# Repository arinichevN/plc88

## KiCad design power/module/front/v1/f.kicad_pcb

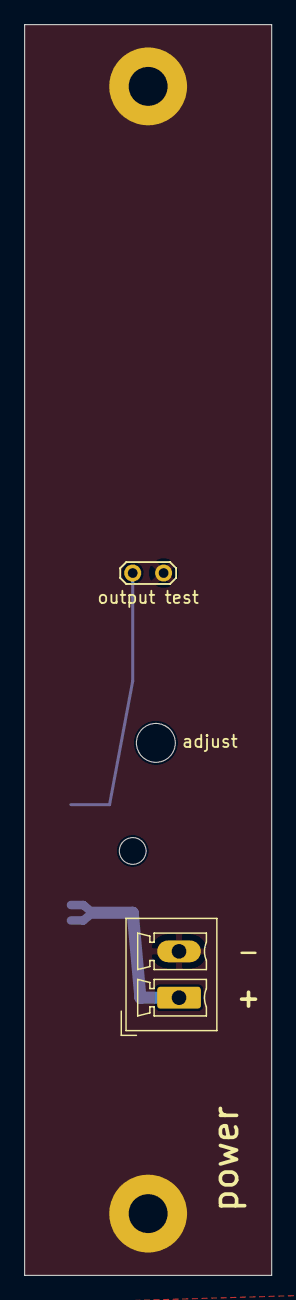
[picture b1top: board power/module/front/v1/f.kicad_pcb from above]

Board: 2 copper layers, 20.3 x 102.9 mm, 7 parts (0 on the bottom side), 3 nets.

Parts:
H1, H2: MountingHole_Pad; MountingHole_3.2mm_M3_Pad
H3: adjust; MountingHole_3.2mm_M3_DIN965
H4: power led; MountingHole_2.2mm_M2_DIN965
J1: fm_power_i
J10: input; PhoenixContact_MCV_1,5_2-G-3.81_1x02_P3.81mm_Vertical
TP1: output test; TestPoint_2Pads_Pitch2.54mm_Drill0.8mm

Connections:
GND: H1.1, H2.1, J1.2, J1.4, J1.5, J10.2, TP1.2
VIN: J1.1, J10.1
VOUT: J1.3, TP1.1

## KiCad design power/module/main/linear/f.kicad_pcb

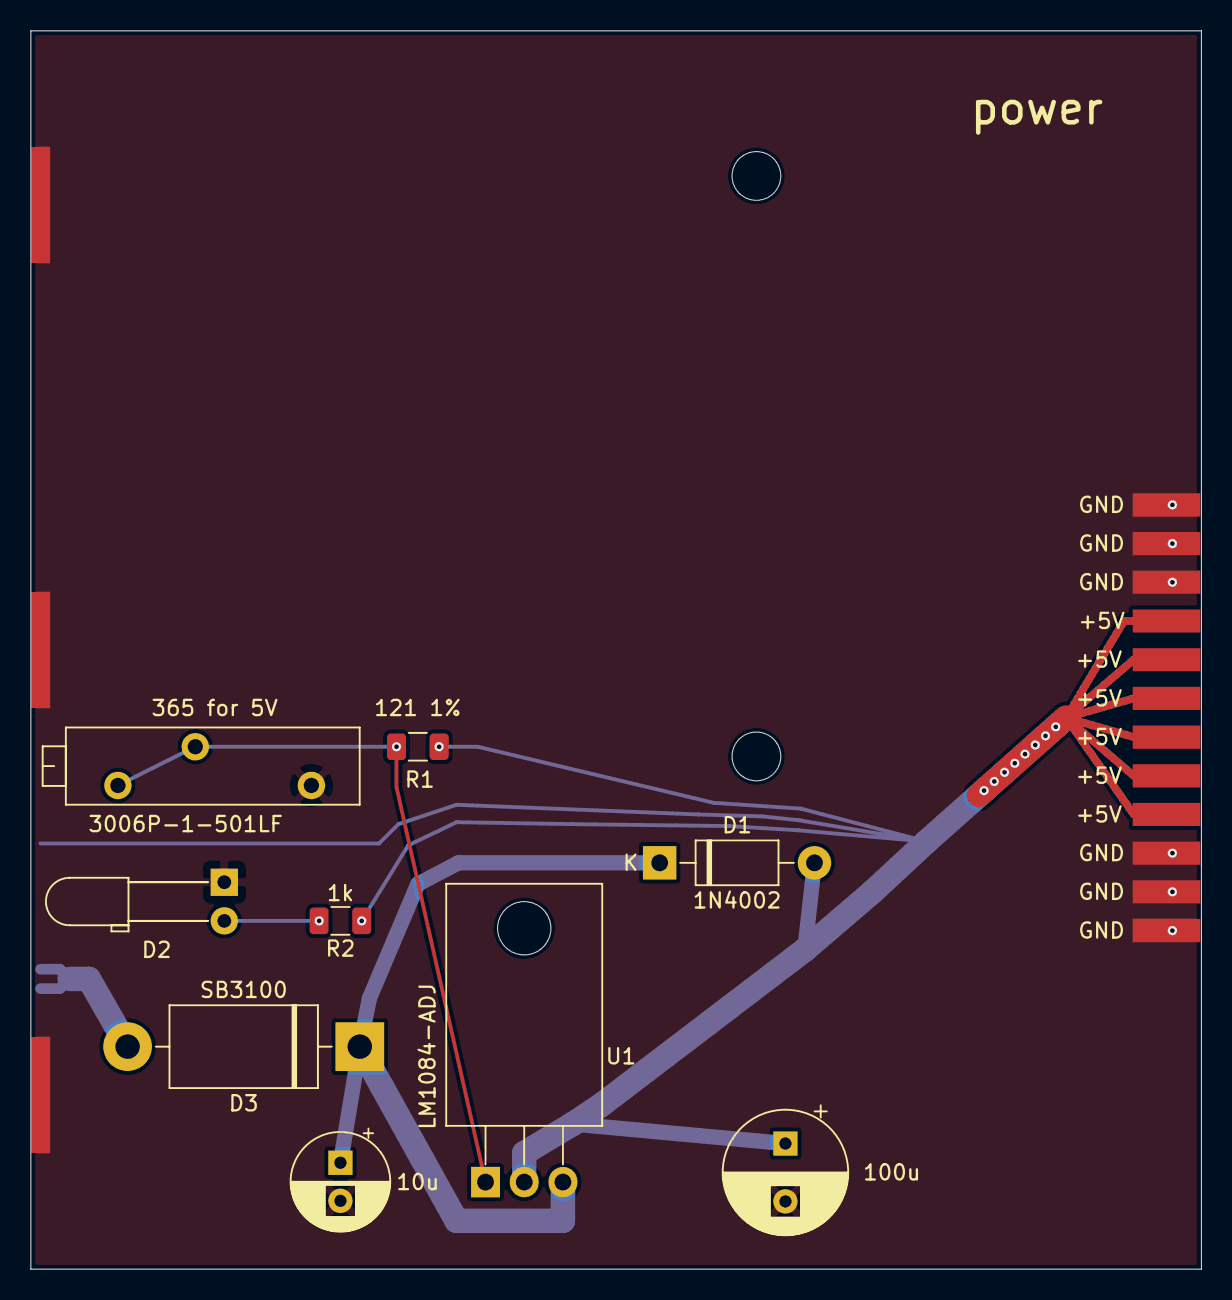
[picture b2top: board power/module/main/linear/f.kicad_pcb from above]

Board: 2 copper layers, 76.8 x 81.3 mm, 13 parts (0 on the bottom side), 6 nets.

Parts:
C1: 10u; CP_Radial_D6.3mm_P2.50mm
C2: 100u; CP_Radial_D8.0mm_P3.80mm
D1: 1N4002; D_DO-41_SOD81_P10.16mm_Horizontal
D2: LED; LED_D3.0mm_Horizontal_O6.35mm_Z2.0mm
D3: SB3100; D_DO-201AD_P15.24mm_Horizontal
H1, H2: MountingHole; MountingHole_3.2mm_M3_DIN965
J1: bus_power_i; bus_power_im
J2: fm_power_i; fm_power_im
R1: 121 1%; R_1206_3216Metric
R2: 1k; R_1206_3216Metric
RV1: 500; Potentiometer_Bourns_3006P_Horizontal
U1: LM1084-ADJ; TO-220-3_Horizontal_TabDown

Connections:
GND: C1.2, C2.2, D2.1, J1.1, J1.2, J1.3, J1.4, J1.5, J1.6, J1.19, J1.20, J1.21, J1.22, J1.23, J1.24, J2.2, J2.4, J2.5, RV1.1
unnamed: C1.1, D1.1, D3.1, U1.3
unnamed: D2.2, R2.2
unnamed: R1.2, RV1.2, RV1.3, U1.1
VIN: D3.2, J2.1
VOUT: C2.1, D1.2, J1.7, J1.8, J1.9, J1.10, J1.11, J1.12, J1.13, J1.14, J1.15, J1.16, J1.17, J1.18, J2.3, R1.1, R2.1, U1.2

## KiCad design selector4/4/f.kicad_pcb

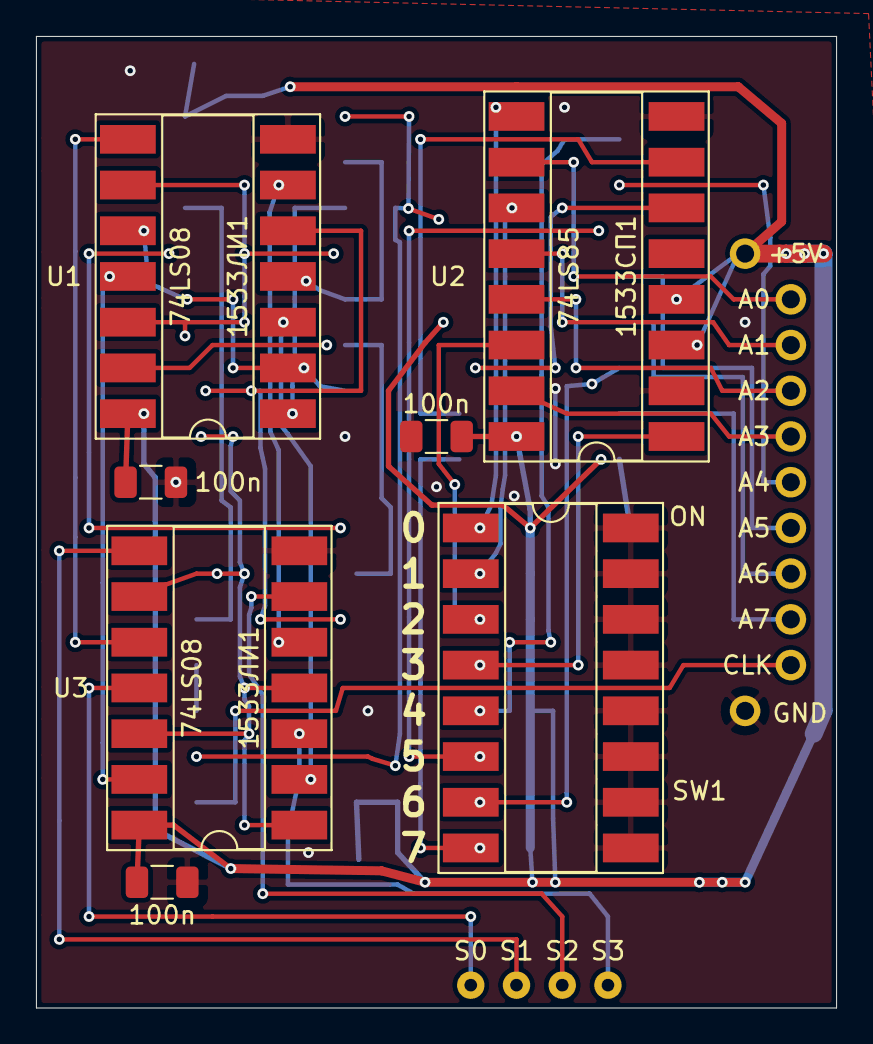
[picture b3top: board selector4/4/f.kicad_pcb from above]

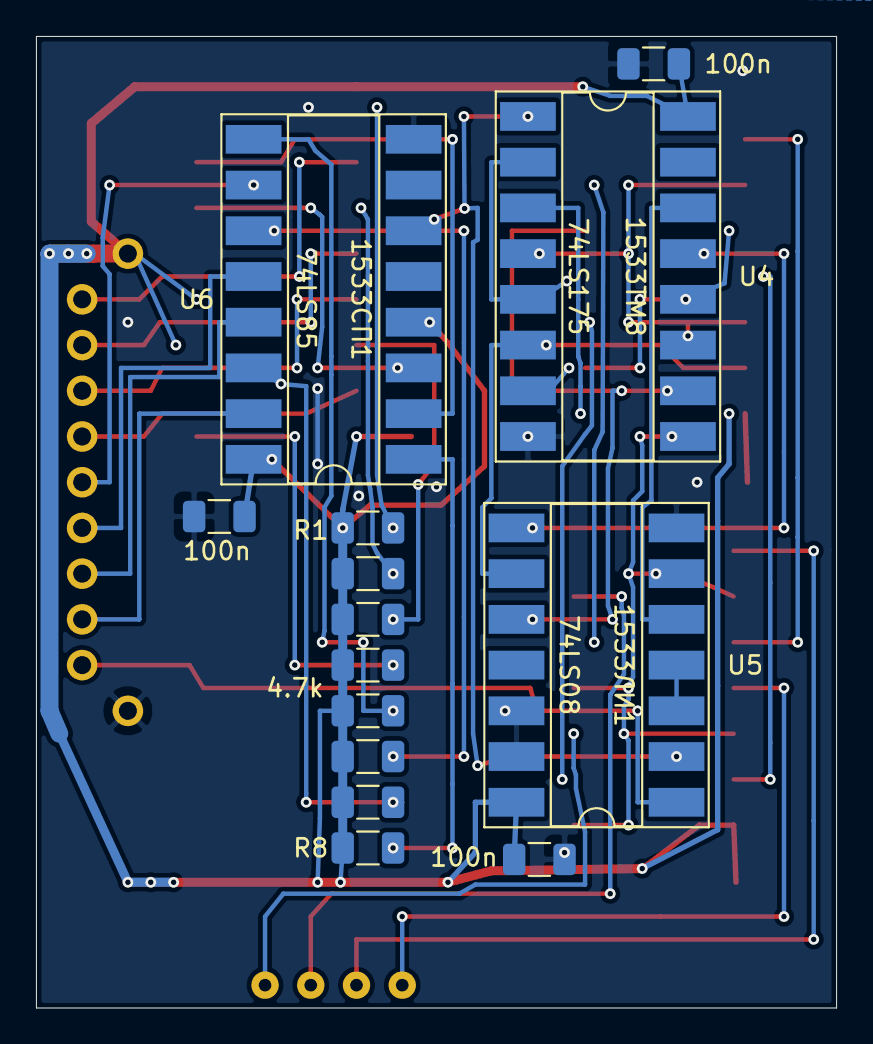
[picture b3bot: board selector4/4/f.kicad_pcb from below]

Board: 2 copper layers, 44.5 x 54.0 mm, 22 parts (14 on the bottom side), 40 nets.

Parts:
C1, C2, C3, C4, C5, C6: 100n; C_1206_3216Metric
J1: selector4_i; selector4_im
R1, R2, R3, R4, R5, R6, R7, R8: 4.7k; R_1206_3216Metric
SW1: SW_DIP_x08; DIP-16_W8.89mm_SMDSocket_LongPads
U1, U3, U5: 74LS08; DIP-14_W8.89mm_SMDSocket_LongPads
U2, U6: 74LS85; DIP-16_W8.89mm_SMDSocket_LongPads
U4: 74LS175; DIP-16_W8.89mm_SMDSocket_LongPads

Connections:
+5V: C1.1, C2.1, C3.1, C4.1, C5.1, C6.1, J1.1, R1.1, R2.1, R3.1, R4.1, R5.1, R6.1, R7.1, R8.1, U1.14, U2.3, U2.4, U2.16, U3.14, U4.16, U5.14, U6.4, U6.16
A0: J1.2, U2.10
A1: J1.3, U2.12
A2: J1.4, U2.13
A3: J1.5, U2.15
A4: J1.6, U6.10
A5: J1.7, U6.12
A6: J1.8, U6.13
A7: J1.9, U6.15
ADDR_OK: U4.1, U5.2, U6.6
B0: R1.2, SW1.1, U2.9
B1: R2.2, SW1.2, U2.11
B2: R3.2, SW1.3, U2.14
B3: R4.2, SW1.4, U2.1
B4: R5.2, SW1.5, U6.9
B5: R6.2, SW1.6, U6.11
B6: R7.2, SW1.7, U6.14
B7: R8.2, SW1.8, U6.1
CLK: J1.10, U5.1
CLK_AFB: U3.1, U3.4, U3.9, U3.12, U4.9, U5.6
FB: U4.14, U5.5
GND: C1.2, C2.2, C3.2, C4.2, C5.2, C6.2, J1.11, SW1.9, SW1.10, SW1.11, SW1.12, SW1.13, SW1.14, SW1.15, SW1.16, U1.7, U2.2, U2.8, U3.7, U4.8, U5.7, U5.12, U5.13, U6.8
unnamed: U1.3, U3.2
unnamed: U1.6, U3.5
unnamed: U1.8, U3.10
unnamed: U1.11, U3.13
unnamed: U2.6, U6.3
unnamed: U2.7, U6.2
unnamed: U4.13, U5.8
unnamed: U5.3, U5.4
P1: U1.9, U1.12, U4.4, U4.11
P2: U1.1, U4.3
P3: U1.4, U4.2, U4.5
P4: U1.13, U4.6, U5.9
P5: U1.2, U1.10, U4.7, U4.12
P6: U1.5, U4.10, U5.10
S0: J1.12, U3.11
S1: J1.13, U3.8
S2: J1.14, U3.6
S3: J1.15, U3.3

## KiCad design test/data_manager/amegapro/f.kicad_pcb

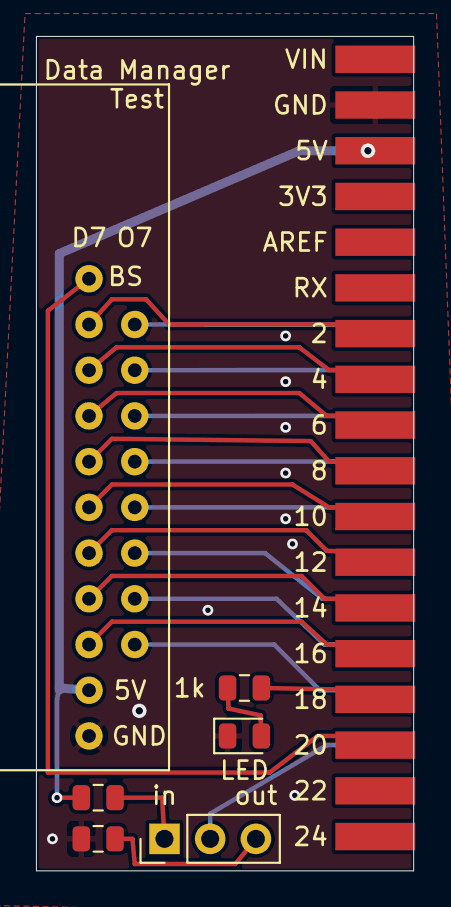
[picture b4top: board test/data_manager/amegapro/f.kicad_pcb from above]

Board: 2 copper layers, 21.0 x 46.4 mm, 7 parts (0 on the bottom side), 24 nets.

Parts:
D1: LED; LED_0805_2012Metric
J1: data_manager_i
J2: arduino mega pro; arduino_mega_pro_2x18_edge
JP1: Jumper_3_Open; PinHeader_1x03_P2.54mm_Vertical
R1: 1k; R_0805_2012Metric
R2, R3: 4.7k; R_0805_2012Metric

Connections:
+5V: J1.18, J2.5, J2.6, R2.2
BS: J1.19, J2.32
D0: J1.2, J2.28
D1: J1.4, J2.26
D2: J1.6, J2.24
D3: J1.8, J2.22
D4: J1.10, J2.20
D5: J1.12, J2.18
D6: J1.14, J2.16
D7: J1.16, J2.14
GND: D1.1, J1.17, J2.3, J2.4, R3.1
LED: J2.30, R1.2
MODE: J2.31, JP1.2
unnamed: D1.2, R1.1
unnamed: JP1.1, R2.1
unnamed: JP1.3, R3.2
O0: J1.1, J2.29
O1: J1.3, J2.27
O2: J1.5, J2.25
O3: J1.7, J2.21
O4: J1.9, J2.19
O5: J1.11, J2.17
O6: J1.13, J2.15
O7: J1.15, J2.13

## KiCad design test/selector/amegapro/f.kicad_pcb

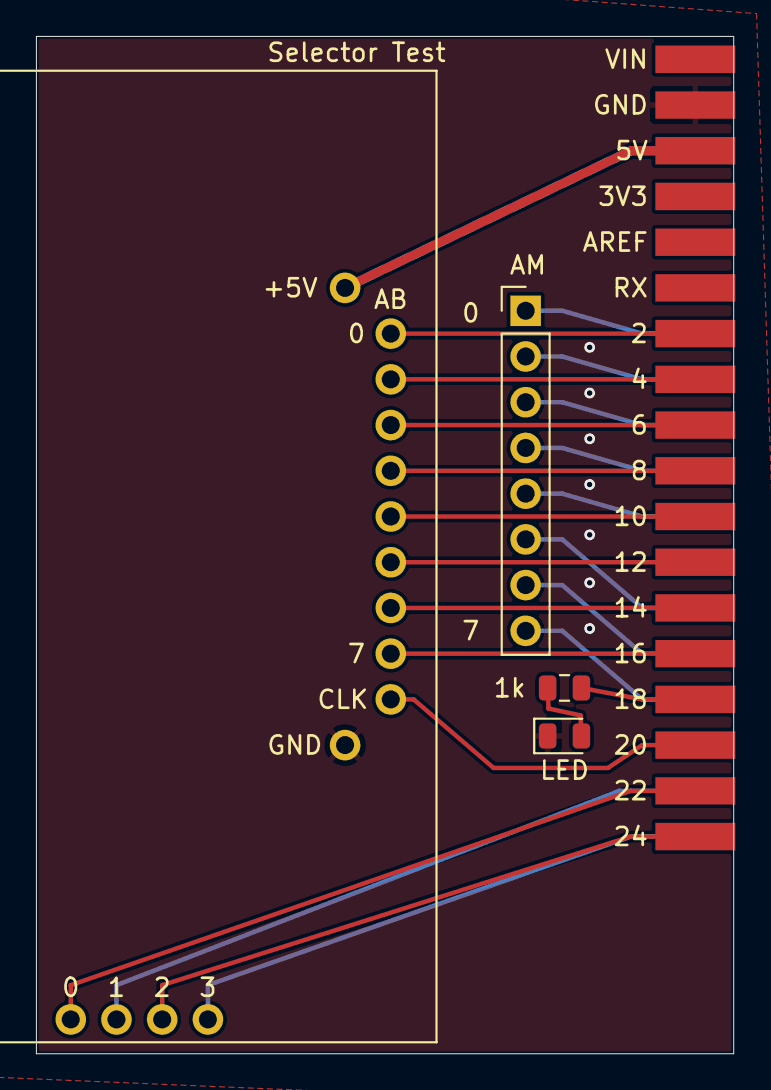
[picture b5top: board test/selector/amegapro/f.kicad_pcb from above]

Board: 2 copper layers, 38.7 x 56.5 mm, 5 parts (0 on the bottom side), 25 nets.

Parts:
D1: LED; LED_0805_2012Metric
J1: selector4_i
J2: arduino mega pro; arduino_mega_pro_2x18_edge
J3: module address; PinHeader_1x08_P2.54mm_Vertical
R1: 1k; R_0805_2012Metric

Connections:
+5V: J1.1, J2.5, J2.6
AB0: J1.2, J2.14
AB1: J1.3, J2.16
AB2: J1.4, J2.18
AB3: J1.5, J2.20
AB4: J1.6, J2.22
AB5: J1.7, J2.24
AB6: J1.8, J2.26
AB7: J1.9, J2.28
AM0: J2.13, J3.1
AM1: J2.15, J3.2
AM2: J2.17, J3.3
AM3: J2.19, J3.4
AM4: J2.21, J3.5
AM5: J2.25, J3.6
AM6: J2.27, J3.7
AM7: J2.29, J3.8
CLK: J1.10, J2.32
GND: D1.1, J1.11, J2.3, J2.4
LED: J2.30, R1.2
unnamed: D1.2, R1.1
S0: J1.12, J2.34
S1: J1.13, J2.33
S2: J1.14, J2.36
S3: J1.15, J2.35

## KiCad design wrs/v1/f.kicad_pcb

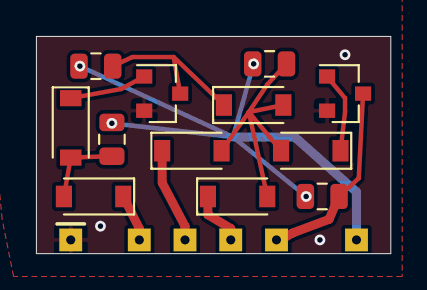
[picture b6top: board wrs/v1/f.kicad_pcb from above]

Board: 2 copper layers, 19.7 x 12.1 mm, 13 parts (0 on the bottom side), 11 nets.

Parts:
D1, D2, D3, D4, D5, D6: 1N4148W; D_SOD-123
J1: wrs_i; wrs_im
Q1, Q2: BC817; SOT-23
R1, R3: 4.7k; R_0805_2012Metric
R2, R4: 1k; R_0805_2012Metric

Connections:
+5V: J1.6, R1.1, R2.1, R3.1, R4.1
GND: J1.1, Q1.2, Q2.2
unnamed: D1.2, D2.2, R1.2
unnamed: D2.1, Q1.1
unnamed: D3.1, Q1.3, R2.2
unnamed: D3.2, D4.2, D5.2, D6.2, R3.2
unnamed: D5.1, Q2.1
S: D6.1, J1.4
SOUT: J1.5, Q2.3, R4.2
WR: D4.1, J1.3
WRN: D1.1, J1.2
